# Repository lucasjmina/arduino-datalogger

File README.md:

# Arduino based datalogger

Enviroment variables are important for ecological studies because they affect the life cicle and
behaviour of organisms. Obtaining a trustworthy record of these variables require the use of
dataloggers, that can be quite expensive.  
Our objective is developing a datalogger more accesible and versatile than comercial available ones,
this could allow an increase in the data volume or making available a trustworthy way of recording
enviromental variables for small investigation groups.  
This repository corresponds to the first prototipe, codename "Oreo".

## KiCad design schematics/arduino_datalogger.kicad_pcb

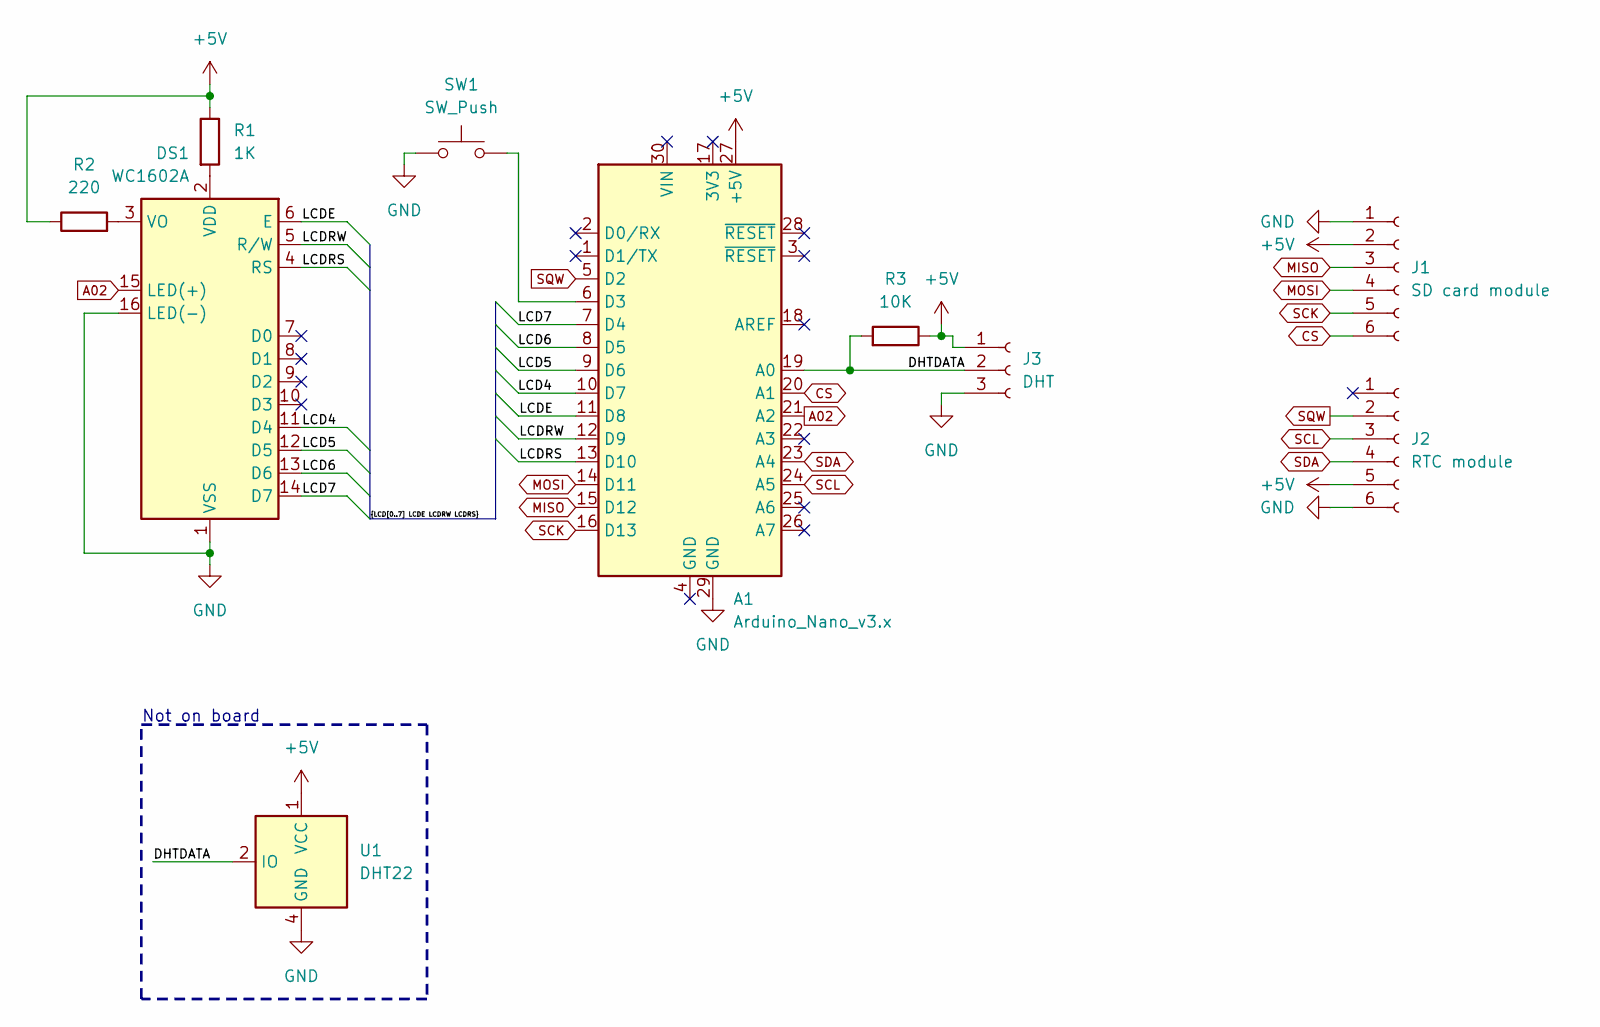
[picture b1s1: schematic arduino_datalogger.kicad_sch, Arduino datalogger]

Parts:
A1: Arduino_Nano_v3.x; Arduino_Nano
DS1: WC1602A
J1: SD card module; PinSocket_1x06_P2.54mm_Vertical
J2: RTC module; PinSocket_1x06_P2.54mm_Vertical
J3: DHT; PinSocket_1x06_P2.54mm_Vertical
R1: 1K; R_Axial_DIN0207_L6.3mm_D2.5mm_P7.62mm_Horizontal
R2: 220; R_Axial_DIN0207_L6.3mm_D2.5mm_P7.62mm_Horizontal
R3: 10K; R_Axial_DIN0207_L6.3mm_D2.5mm_P7.62mm_Horizontal
SW1: SW_Push; SW_PUSH-12mm
U1: DHT22; Aosong_DHT11_5.5x12.0_P2.54mm

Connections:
+5V: A1.27 (+5V), J1.2, J2.5, J3.1, R1.1, R2.1, R3.1, U1.1 (VCC)
/DHTDATA: A1.19 (A0), J3.2, R3.2, U1.2 (IO)
/LCD4: A1.10 (D7), DS1.11 (D4)
/LCD5: A1.9 (D6), DS1.12 (D5)
/LCD6: A1.8 (D5), DS1.13 (D6)
/LCD7: A1.7 (D4), DS1.14 (D7)
/LCDE: A1.11 (D8), DS1.6 (E)
/LCDRS: A1.13 (D10), DS1.4 (RS)
/LCDRW: A1.12 (D9), DS1.5 (R/W)
A02: A1.21 (A2), DS1.15 (LED(+))
CS: A1.20 (A1), J1.6
GND: A1.29 (GND), DS1.1 (VSS), DS1.16 (LED(-)), J1.1, J2.6, J3.3, SW1.1, U1.4 (GND)
MISO: A1.15 (D12), J1.3
MOSI: A1.14 (D11), J1.4
unnamed: A1.6 (D3), SW1.2
unnamed: DS1.2 (VDD), R1.2
unnamed: DS1.3 (VO), R2.2
SCK: A1.16 (D13), J1.5
SCL: A1.24 (A5), J2.3
SDA: A1.23 (A4), J2.4
SQW: A1.5 (D2), J2.2

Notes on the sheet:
Not on board

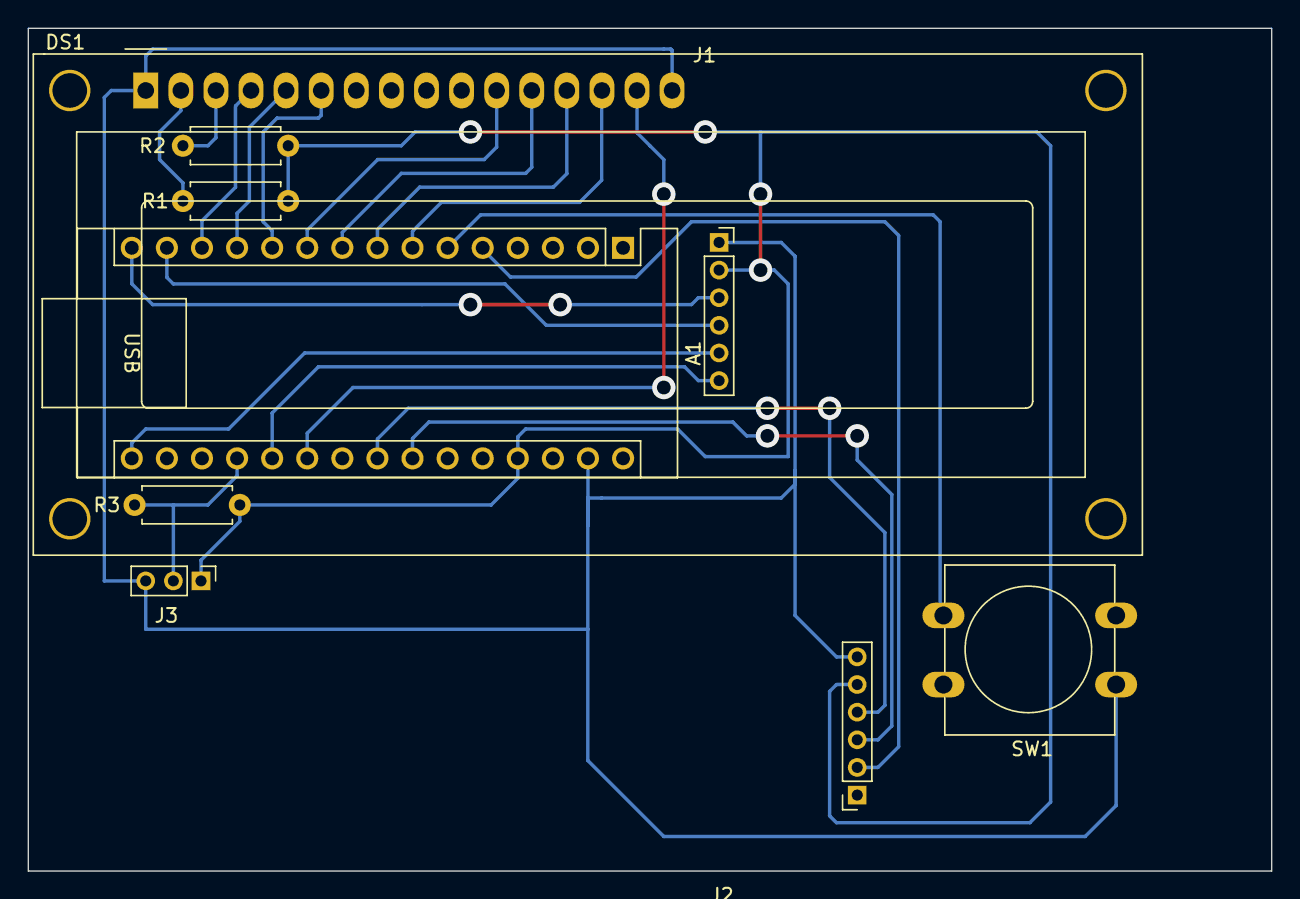
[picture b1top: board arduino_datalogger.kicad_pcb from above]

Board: 2 copper layers, 90.0 x 61.0 mm, 9 parts (0 on the bottom side), 21 nets.

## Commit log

2023-10-10 Cambios para Arduino Nano
2023-10-11 Botón para prender LCD y cambios en interrupts
    Botón enciende el balcklight del lcd y lo apaga después de un tiempo. Resulta que no se puede leer los valores del DHT dentro de un interrupt, así que eso pasó a estar dentro de loop, el interrupt so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
2023-10-12 Solucionado posible problema con el overflow de millis()
2023-10-12 Ahora se suspende durante inactividad
    Falta medir el consumo
2023-10-12 Agregado un condicional para chequear si el archivo existe o no
    Si existe se detiene el programa
2023-10-14 Cambios en la declaracion de algunas variables. Cadigo de la función 'write_sd()' movido a loop y eliminada esa función
2023-10-18 Variables definidas en void loop() estaban causando algunos problemas, se definieron como globales
2023-10-23 Esquema circuito
2023-10-24 Algunos cambios esquema
2023-10-24 Diseñando PCB
2023-10-24 Teniendo en cuenta las medidas reales de los modulos
2023-10-25 Simbolo y footprint para modulo RTC y lector de SD
2023-10-25 Eliminado el uso de pin 13 como salida
    No me di cuenta que estaba usando el pin 13, que es el mismo que se usa
    para SPI, como salida para un led de testigo.
2023-11-06 Simbolos y footprints para modulo RTC y microSD
2023-11-06 Preparando gitignore para migrar a PlatformIO
2023-11-06 Inicializando proyecto de PlatformIO
    https://platformio.org/
2023-11-06 Eliminado PCB y footprints personalizadas
    Decidimos hacer el prototipo en perfboard, así que ya no es necesario lo anterior
2023-11-06 Librerias necesarias
2023-11-06 Arreglando definición de función 'sleep_time()'
2023-11-10 Placa correcta es nanoatmega328new
2023-11-10 Algunos cambios en el primer bloque de comentarios
2023-11-10 Corregidas conexiones de LCD
    VO estaba conectado a Vcc con una R de 220 (debe ir a GND con R de 1K).
    Vss tenia una R de 1K (debe tener una de 220).
2023-11-13 Cambio nombre de carpeta 'schematics' a 'board'
2023-11-17 Movido proyecto a carpeta 'prototipo'
2023-11-17 Hojas de datos relevantes
2023-12-02 Documentación
    Hojas de datos y diagramas de pines
2023-12-02 Cambio de nombre
2023-12-02 Cambios menores en esquema y generado PDF
2023-12-02 Cambios en encabezado, agregado directiva de compilación para hora del RTC
2023-12-03 Cambio de carpeta
2023-12-03 README.md
2023-12-07 feat: Nombre de archivo único
    Generación de un archivo único cada vez que se inicia, utilizando un
    timestamp generado por el RTC. De la siguiente forma
    "YYYMMDDhhmmss_DATALOG.csv".
2023-12-18 refactor: Cambiada libreria para SD
    arduino-libraries/SD cambiada por greiman/SdFat.
2023-12-18 Makefile para más comodidad
2023-12-18 refactor: Translation to English
    Decided to use English from now on, everything will be translated.
2023-12-18 fix: Fixed check command in Makefile
2023-12-18 refactor: README translated
    README.md transtalated to English. Spanish version kept as "README.es.md".
2023-12-18 refactor: Added newline
    I forgot the double space 🤡
2023-12-18 Traslation of schematic to English
2023-12-19 Show SD free space when powering on
